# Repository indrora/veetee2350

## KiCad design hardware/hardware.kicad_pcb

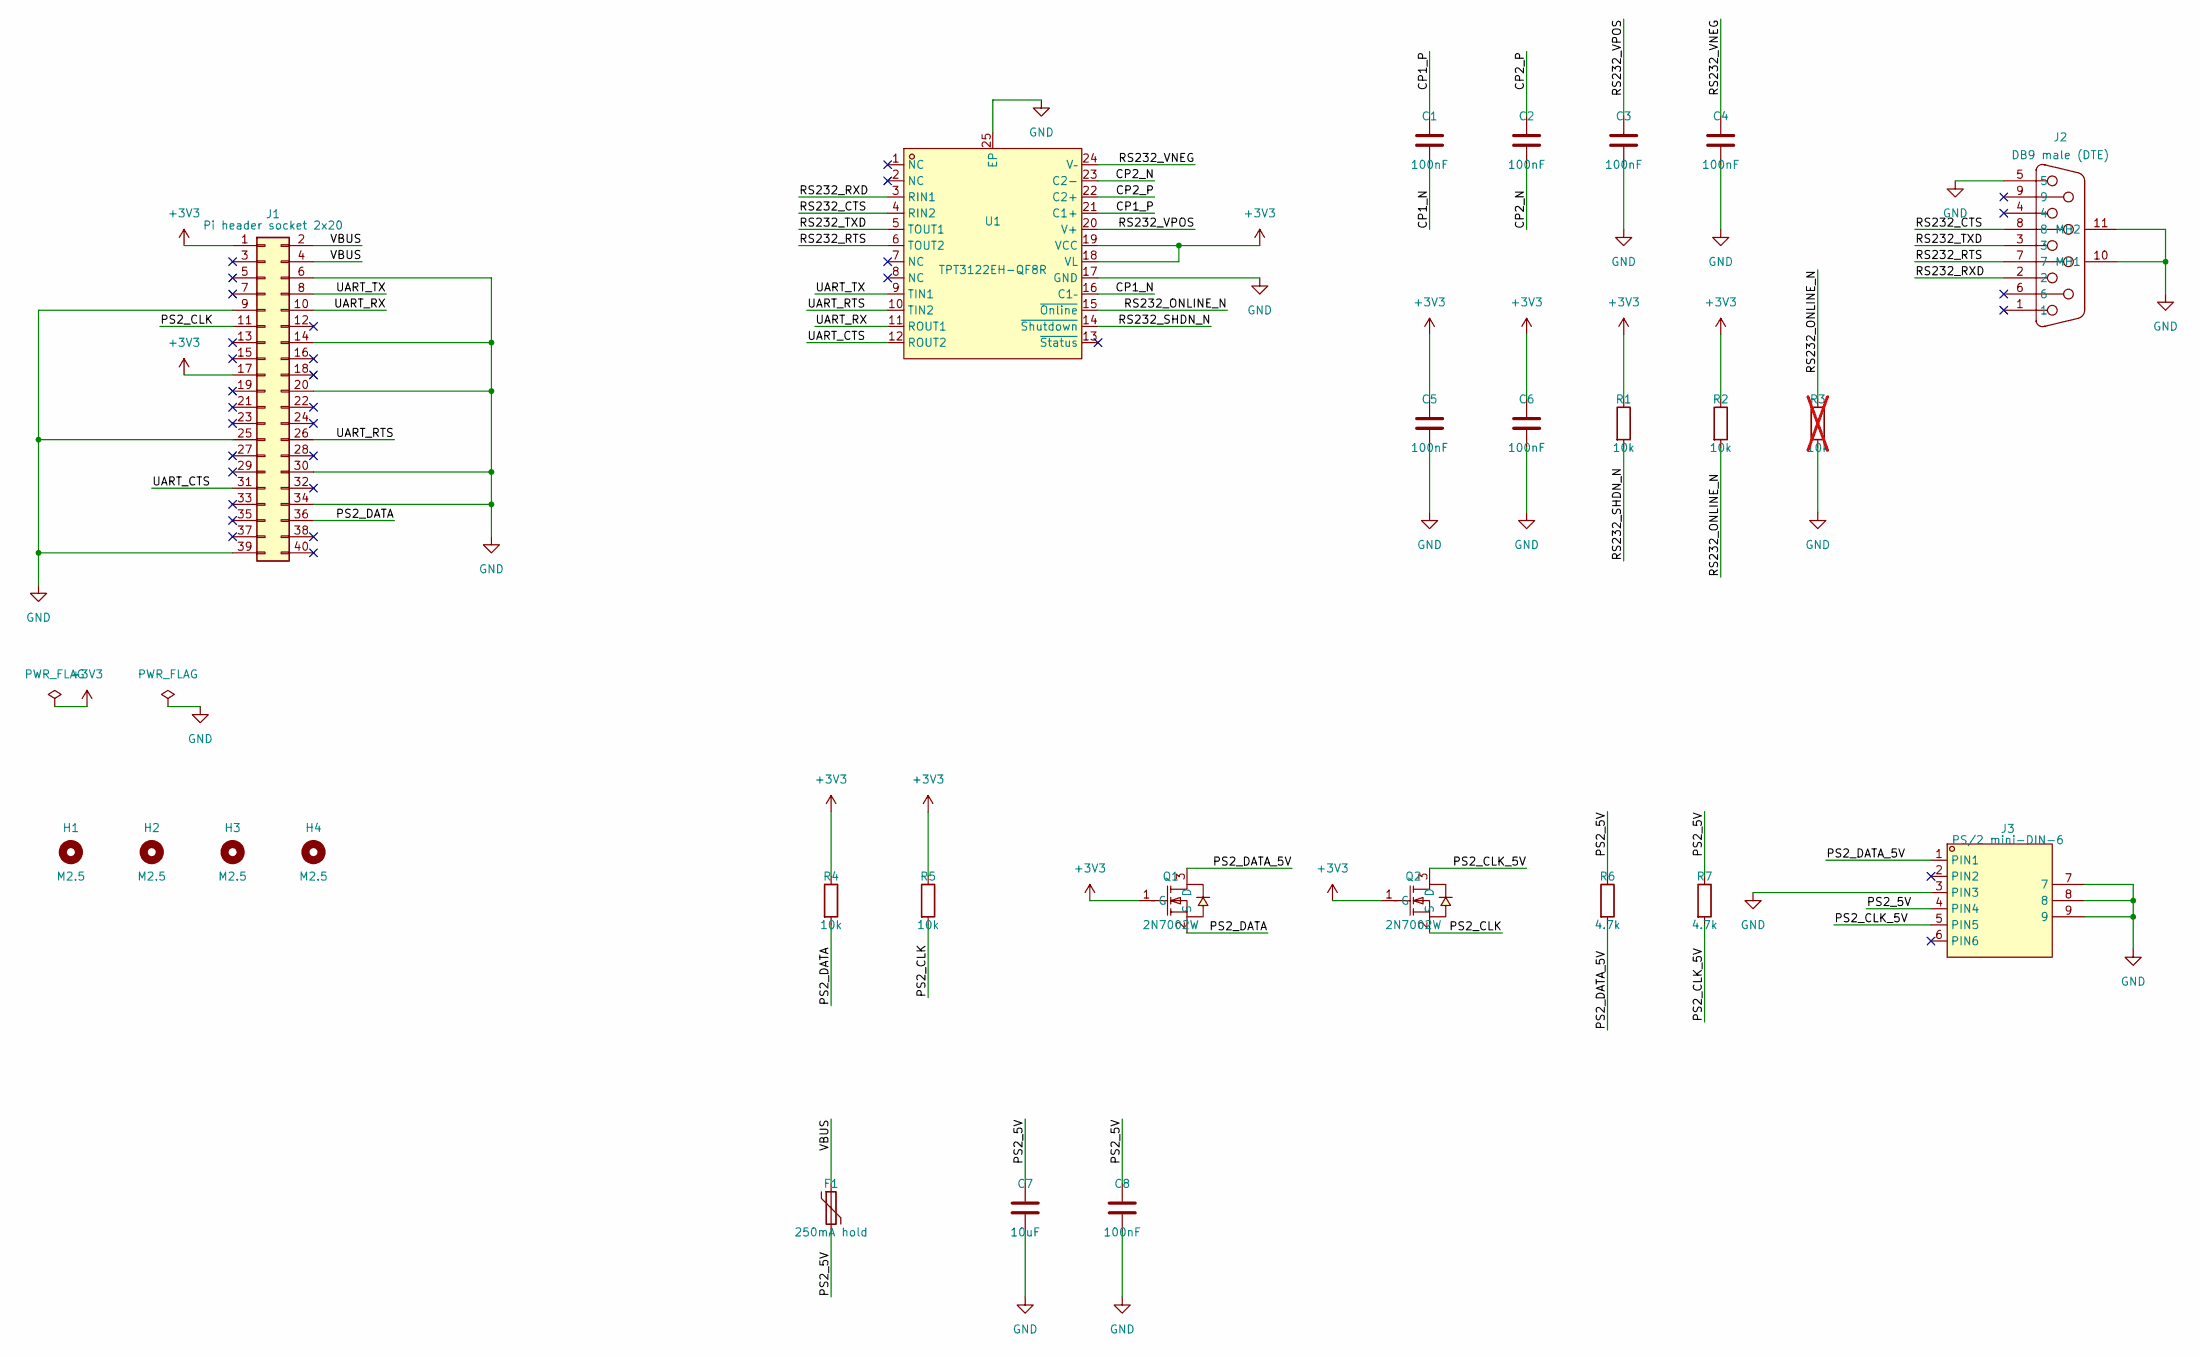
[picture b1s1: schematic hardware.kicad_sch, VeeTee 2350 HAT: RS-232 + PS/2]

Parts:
C1, C2, C3, C4, C5, C6, C8: 100nF; C_0603_1608Metric; LCSC C14663
C7: 10uF; C_0603_1608Metric; LCSC C19702
F1: 250mA hold; Fuse_1206_3216Metric; LCSC C70069
H1, H2, H3, H4: M2.5; MountingHole_2.7mm_M2.5
J1: Pi header socket 2x20; PinSocket_2x20_P2.54mm_Vertical; LCSC TBD
J2: DB9 male (DTE); DSUB-TH_DMR-9P; LCSC C141880
J3: PS/2 mini-DIN-6; CONN-TH_DS1093-01-PN60; LCSC C77848
Q1, Q2: 2N7002W; SOT-323-3_L2.0-W1.3-P1.30-LS2.1-BR; LCSC C7420322
R1, R2, R4, R5: 10k; R_0603_1608Metric; LCSC C25804
R3: 10k; R_0603_1608Metric; LCSC C25804; not fitted
R6, R7: 4.7k; R_0603_1608Metric; LCSC C23162
U1: TPT3122EH-QF8R; QFN-24_L4.0-W4.0-P0.50-TL-EP2.7; LCSC C19188736

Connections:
+3V3: C5.1, C6.1, J1.1, J1.17, Q1.1 (G), Q2.1 (G), R1.1, R2.1, R4.1, R5.1, U1.18 (VL), U1.19 (VCC)
/CP1_N: C1.2, U1.16 (C1–)
/CP1_P: C1.1, U1.21 (C1+)
/CP2_N: C2.2, U1.23 (C2-)
/CP2_P: C2.1, U1.22 (C2+)
/PS2_5V: C7.1, C8.1, F1.2, J3.4 (PIN4), R6.1, R7.1
/PS2_CLK: J1.11, Q2.2 (S), R5.2
/PS2_CLK_5V: J3.5 (PIN5), Q2.3 (D), R7.2
/PS2_DATA: J1.36, Q1.2 (S), R4.2
/PS2_DATA_5V: J3.1 (PIN1), Q1.3 (D), R6.2
/RS232_CTS: J2.8, U1.4 (RIN2)
/RS232_ONLINE_N: R2.2, R3.1, U1.15 (~Online)
/RS232_RTS: J2.7, U1.6 (TOUT2)
/RS232_RXD: J2.2, U1.3 (RIN1)
/RS232_SHDN_N: R1.2, U1.14 (~Shutdown)
/RS232_TXD: J2.3, U1.5 (TOUT1)
/RS232_VNEG: C4.1, U1.24 (V–)
/RS232_VPOS: C3.1, U1.20 (V+)
/UART_CTS: J1.31, U1.12 (ROUT2)
/UART_RTS: J1.26, U1.10 (TIN2)
/UART_RX: J1.10, U1.11 (ROUT1)
/UART_TX: J1.8, U1.9 (TIN1)
/VBUS: F1.1, J1.2, J1.4
GND: C3.2, C4.2, C5.2, C6.2, C7.2, C8.2, J1.6, J1.9, J1.14, J1.20, J1.25, J1.30, J1.34, J1.39, J2.5, J2.10 (MH1), J2.11 (MH2), J3.3 (PIN3), J3.7, J3.8, J3.9, R3.2, U1.17 (GND), U1.25 (EP)

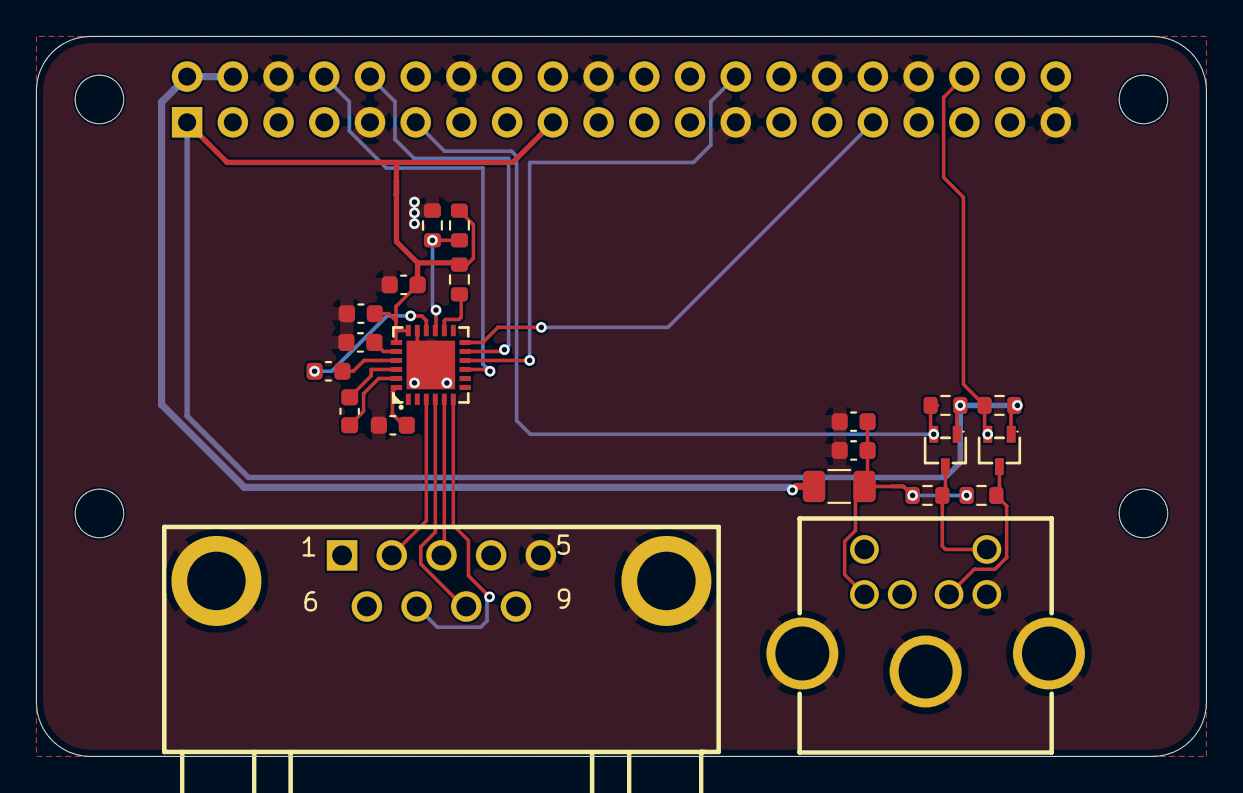
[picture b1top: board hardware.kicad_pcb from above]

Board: 2 copper layers, 65.0 x 40.0 mm, 26 parts (1 on the bottom side), 24 nets.

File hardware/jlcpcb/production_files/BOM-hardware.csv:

Comment,Designator,Footprint,LCSC,Quantity
100nF,"C1,C2,C3,C4,C5,C6,C8",C_0603_1608Metric,C14663,7
10k,"R1,R2,R4,R5",R_0603_1608Metric,C25804,4
10uF,C7,C_0603_1608Metric,C19702,1
250mA hold,F1,Fuse_1206_3216Metric,C70069,1
2N7002W,"Q1,Q2",SOT-323-3_L2.0-W1.3-P1.30-LS2.1-BR,C7420322,2
4.7k,"R6,R7",R_0603_1608Metric,C23162,2
DB9 male (DTE),J2,DSUB-TH_DMR-9P,C141880,1
PS/2 mini-DIN-6,J3,CONN-TH_DS1093-01-PN60,C77848,1
TPT3122EH-QF8R,U1,QFN-24_L4.0-W4.0-P0.50-TL-EP2.7,C19188736,1
